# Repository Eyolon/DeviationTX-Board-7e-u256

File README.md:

# DeviationTX-Board-7e-u256

Designed with EAGLE https://www.autodesk.fr/products/eagle/free-download

This board use https://stm32-base.org/boards/STM32F103RCT6-STM32-Mini-V2.0.html and asume the flash on the board is used. (you have to unsold the pin of the cs flash and wire to the good point (TODO: provide a photo from the post for this point)

## BOM
### Screen
there is 2 possibility for the screen. Original from a DEVO 7e or SSD1306 (but you need a prticular firmware for this  !)

### Radio module
radio pins is designed to provide easyly what you need for a 4 in 1 module or mod to use 4 radio module.

### Lazy power management mod
If you dont want try to sold SMD parts, use :
* 2 5V booster like the DD0505MC (10a45 5v booster) 
* external charger/protector for a lipo battery (like a TP4056 shield for 18650 or lipo)

### Power management
If you are courageous you need :
* 2 10A45
* 1 TP4056
* 1 8205A
* TODO

### Plugs
JST-PH 2.5

### Other parts (buzzer and vibrator part):
* SS8050 ("Y1")
* SS8550 ("Y2")

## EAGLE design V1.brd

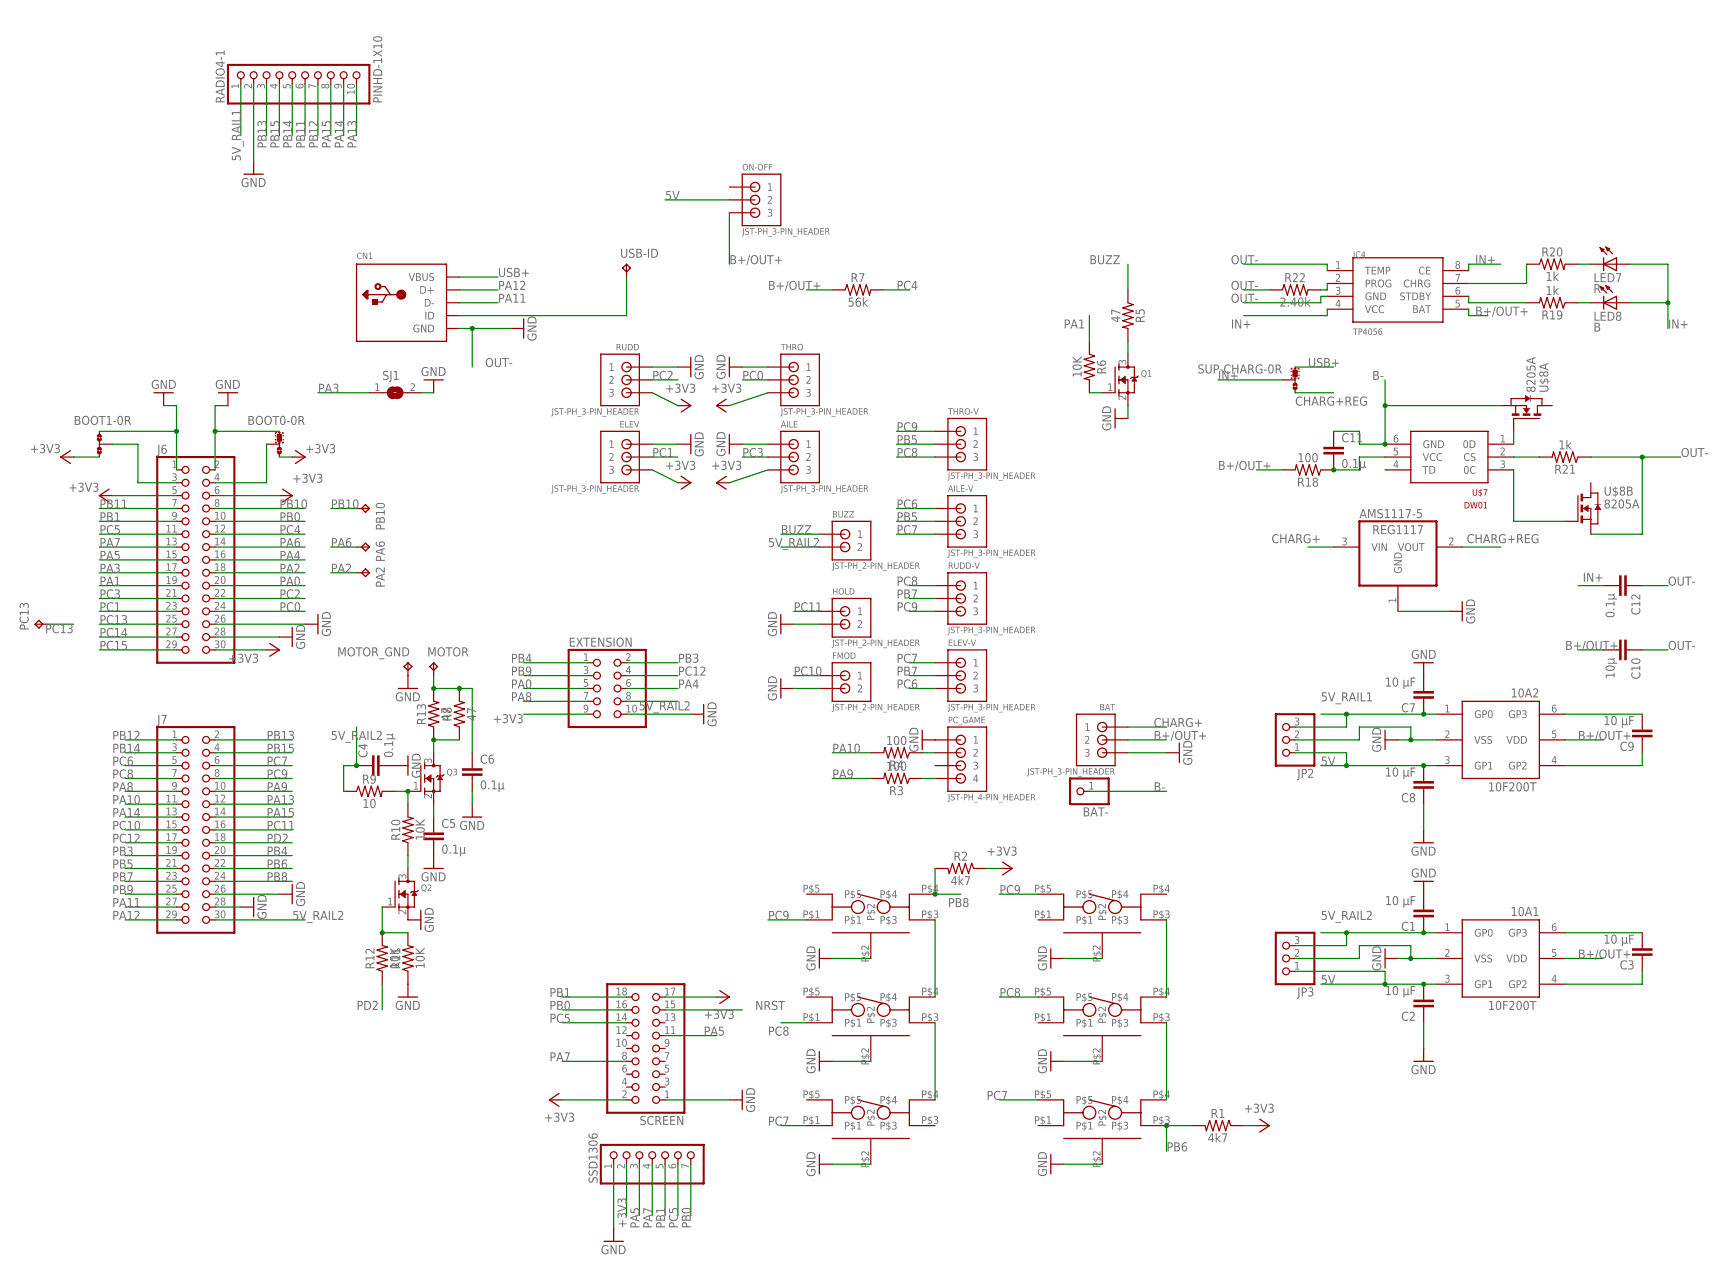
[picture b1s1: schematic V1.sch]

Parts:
10A1, 10A2: 10F200T; SOT23-6
AILE: JST-PH_3-PIN_HEADER; JST_B3B-PH_HEADER
AILE-V: JST-PH_3-PIN_HEADER; JST_B3B-PH_HEADER
AMS1117-5: REG1117; SOT223
BAT: JST-PH_3-PIN_HEADER; JST_B3B-PH_HEADER
BAT-: PINHD-1X1; 1X01
BOOT0, BOOT1: 0R-JUMPC; C0R-JMP
BUZZ: JST-PH_2-PIN_HEADER; JST_B2B-PH_HEADER
C1, C2, C3, C7, C8, C9: 10 µF; C0603
C4, C5, C6, C11, C12: 0.1µ; C0603
C10: 10µ; C0603
CN1: USBMINIB; USB-MINIB
DN-: TS-1262V-5
ELEV: JST-PH_3-PIN_HEADER; JST_B3B-PH_HEADER
ELEV-V: JST-PH_3-PIN_HEADER; JST_B3B-PH_HEADER
ENT: TS-1262V-5
EXT: TS-1262V-5
EXTENSION: PINHD-2X5; 2X05
FMOD: JST-PH_2-PIN_HEADER; JST_B2B-PH_HEADER
HOLD: JST-PH_2-PIN_HEADER; JST_B2B-PH_HEADER
IC4: TP4056; SOP-8
J6, J7: PINHD-2X15; 2X15
JP2, JP3: PINHD-1X3; 1X03
L-: TS-1262V-5
LED7: R; CHIP-LED0603
LED8: B; CHIP-LED0603
MOTOR: TPTP20R; TP20R
MOTOR_GND: TPTP20R; TP20R
ON-OFF: JST-PH_3-PIN_HEADER; JST_B3B-PH_HEADER
PA2, PA6: TPTP20R; TP20R
PB10: TPTP20R; TP20R
PC13: TPTP20R; TP20R
PC_GAME: JST-PH_4-PIN_HEADER; JST_B4B-PH_HEADER
Q1, Q2, Q3: MOSFET-NREFLOW; SOT23
R1, R2: 4k7; 0603
R3, R4, R18: 100; 0603
R5, R8, R13: 47; 0603
R6, R10, R11, R12: 10K; 0603
R7: 56k; 0603
R9: 10; 0603
R19, R20, R21: 1k; 0603
R22: 2.40k; 0603
R+: TS-1262V-5
RADIO4-1: PINHD-1X10; 1X10-BIG
RUDD: JST-PH_3-PIN_HEADER; JST_B3B-PH_HEADER
RUDD-V: JST-PH_3-PIN_HEADER; JST_B3B-PH_HEADER
SCREEN: PINHD-2X9; 2X09
SJ1: SJ
SSD1306: PINHD-1X7; 1X07
SUP-CHARG: 0R-JUMPC; C0R-JMP
THRO: JST-PH_3-PIN_HEADER; JST_B3B-PH_HEADER
THRO-V: JST-PH_3-PIN_HEADER; JST_B3B-PH_HEADER
U$7: DW01; SOT23-6
U$8: 8205A; TSSOP8
UP+: TS-1262V-5
USB-ID: TPTP20R; TP20R

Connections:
5V: 10A1.3 (GP1), 10A2.3 (GP1), C2.2, C8.2, JP2.1, JP3.1, ON-OFF.P2 (2)
5V_RAIL1: 10A2.1 (GP0), C7.1, JP2.3, RADIO4-1.1
5V_RAIL2: 10A1.1 (GP0), BUZZ.P2 (2), C1.1, C4.1, EXTENSION.8, J7.30, JP3.3, R9.1
+3V3: AILE.P3 (3), BOOT0.3, BOOT1.3, ELEV.P3 (3), EXTENSION.9, J6.5, J6.6, J6.30, R1.1, R2.1, RUDD.P3 (3), SCREEN.2, SCREEN.17, SSD1306.2, THRO.P3 (3)
B+/OUT+: 10A1.5 (VDD), 10A2.5 (VDD), BAT.P2 (2), C10.2, IC4.5 (BAT), ON-OFF.P3 (3), R7.1, R18.2
B-: BAT-.1, C11.1, U$7.6 (GND), U$8.2 (S), U$8.3 (S)
BUZZ: BUZZ.P1 (1), R5.1
CHARG+: AMS1117-5.3 (VIN), BAT.P1 (1)
CHARG+REG: AMS1117-5.2 (VOUT), SUP-CHARG.3
GND: 10A1.2 (VSS), 10A2.2 (VSS), AILE.P1 (1), AMS1117-5.1 (GND), BAT.P3 (3), BOOT0.1, BOOT1.1, C1.2, C2.1, C4.2, C5.2, C6.2, C7.2, C8.1, DN-.P$2, ELEV.P1 (1), ENT.P$2, EXT.P$2, EXTENSION.10, FMOD.P2 (2), HOLD.P2 (2), J6.1, J6.2, J6.26, J6.28, J7.26, J7.28, JP2.2, JP3.2, L-.P$2, MOTOR_GND.TP, PC_GAME.P1 (1), Q1.2 (S), Q2.2 (S), R11.1, R+.P$2, RADIO4-1.2, RUDD.P1 (1), SCREEN.1, SJ1.2, SSD1306.1, THRO.P1 (1), UP+.P$2
IN+: C12.2, IC4.4 (VCC), IC4.8 (CE), LED7.A, LED8.A, SUP-CHARG.2
unnamed: DN-.P$4, UP+.P$3
unnamed: BOOT0.2, J6.4
unnamed: BOOT1.2, J6.3
unnamed: EXT.P$3, UP+.P$4
unnamed: ENT.P$4, R+.P$3
unnamed: L-.P$3, R+.P$4
unnamed: 10A1.6 (GP3), C3.2
unnamed: Q2.3 (D), R10.1
unnamed: 10A1.4 (GP2), C3.1
unnamed: Q3.1 (G), R9.2, R10.2
unnamed: Q2.1 (G), R11.2, R12.2
unnamed: CN1.ID, USB-ID.TP
unnamed: PC_GAME.P2 (2), R4.1
unnamed: PC_GAME.P4 (4), R3.1
unnamed: Q1.3 (D), R5.2
unnamed: Q1.1 (G), R6.2
unnamed: C6.1, MOTOR.TP, R8.2, R13.2
unnamed: Q3.3 (D), R8.1, R13.1
unnamed: 10A2.6 (GP3), C9.2
unnamed: C5.1, Q3.2 (S)
unnamed: 10A2.4 (GP2), C9.1
unnamed: LED8.C, R19.1
unnamed: U$7.1 (0D), U$8.4 (G)
unnamed: U$7.3 (0C), U$8.5 (G)
unnamed: R21.2, U$7.2 (CS)
unnamed: C11.2, R18.1, U$7.5 (VCC)
unnamed: IC4.6 (STDBY), R19.2
unnamed: IC4.7 (CHRG), R20.1
unnamed: LED7.C, R20.2
unnamed: IC4.2 (PROG), R22.2
NRST: SCREEN.15
OUT-: C10.1, C12.1, CN1.GND, IC4.1 (TEMP), IC4.3 (GND), R21.1, R22.1, U$8.6 (S), U$8.7 (S)
PA0: EXTENSION.5, J6.20
PA1: J6.19, R6.1
PA2: J6.18, PA2.TP
PA3: J6.17, SJ1.1
PA4: EXTENSION.6, J6.16
PA5: J6.15, SCREEN.11, SSD1306.3
PA6: J6.14, PA6.TP
PA7: J6.13, SCREEN.8, SSD1306.4
PA8: EXTENSION.7, J7.9
PA9: J7.10, R3.2
PA10: J7.11, R4.2
PA11: CN1.D-, J7.27
PA12: CN1.D+, J7.29
PA13: J7.12, RADIO4-1.10
PA14: J7.13, RADIO4-1.9
PA15: J7.14, RADIO4-1.8
PB0: J6.10, SCREEN.16, SSD1306.7
PB1: J6.9, SCREEN.18, SSD1306.5
PB3: EXTENSION.2, J7.19
PB4: EXTENSION.1, J7.20
PB5: AILE-V.P2 (2), J7.21, THRO-V.P2 (2)
PB6: ENT.P$3, J7.22, R1.2
PB7: ELEV-V.P2 (2), J7.23, RUDD-V.P2 (2)
PB8: EXT.P$4, J7.24, R2.2
PB9: EXTENSION.3, J7.25
PB10: J6.8, PB10.TP
PB11: J6.7, RADIO4-1.6
PB12: J7.1, RADIO4-1.7
PB13: J7.2, RADIO4-1.3
PB14: J7.3, RADIO4-1.5
PB15: J7.4, RADIO4-1.4
PC0: J6.24, THRO.P2 (2)
PC1: ELEV.P2 (2), J6.23
PC2: J6.22, RUDD.P2 (2)
PC3: AILE.P2 (2), J6.21
PC4: J6.12, R7.2
PC5: J6.11, SCREEN.14, SSD1306.6
PC6: AILE-V.P1 (1), ELEV-V.P3 (3), J7.5
PC7: AILE-V.P3 (3), DN-.P$1, ELEV-V.P1 (1), ENT.P$5, J7.6
PC8: J7.7, R+.P$5, RUDD-V.P1 (1), THRO-V.P3 (3), UP+.P$1
PC9: EXT.P$1, J7.8, L-.P$5, RUDD-V.P3 (3), THRO-V.P1 (1)
PC10: FMOD.P1 (1), J7.15
PC11: HOLD.P1 (1), J7.16
PC12: EXTENSION.4, J7.17
PC13: J6.25, PC13.TP
PC14: J6.27
PC15: J6.29
PD2: J7.18, R12.1
USB+: CN1.VBUS, SUP-CHARG.1

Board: 2 copper layers, 82 parts (21 on the bottom side), 89 nets, no tracks yet.

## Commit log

2020-11-18 Original commit

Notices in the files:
parts and their libraries:
SparkFun-Resistors: Licensing: Creative Commons ShareAlike 4.0 International - https://creativecommons.org/licenses/by-sa/4.0
